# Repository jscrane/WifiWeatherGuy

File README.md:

View this project on [CADLAB.io](https://cadlab.io/project/1280). 

# WiFiWeatherGuy
WeatherGuy for ESP8266.

## Hardware
- Wemos D1 Mini
- ILI9163-based TFT display, see [here](http://henrysbench.capnfatz.com/henrys-bench/arduino-displays/arduino-1-44-in-spi-tft-display-tutorial/)

## Software
- Arduino 1.8.9
- [TFT_eSPI library](https://github.com/Bodmer/TFT_eSPI) 2.5.43
- [ESP8266 for Arduino](https://github.com/esp8266/Arduino.git) 3.1.2
- [Arduino ESP8266 filesystem uploader](https://github.com/esp8266/arduino-esp8266fs-plugin)
- [ArduinoJson](http://arduinojson.org/) 7.2.0
- [Timezone](https://github.com/JChristensen/Timezone) 1.2.4
- [Time](https://github.com/PaulStoffregen/Time) 1.6
- [SimpleTimer](https://github.com/schinken/SimpleTimer)

## Installation
- Get an API key for your Provider (required for OpenWeatherMap, not for Open Meteo)
- Edit data/config.json with your preferences
- Configure your display in TFT_eSPI/User_Setup.h (if using the Arduino IDE), otherwise edit Makefile
- Configure your timezone in zone.h
- Upload the filesystem (Tools > ESP8266 Sketch Data Upload)
- Upload the sketch

## Note
The weather icons must be 24-bit bitmaps; convert from GIF as follows:

    % convert foo.gif -type truecolor foo.bmp 

The [Airycon](https://github.com/HaroleDev/Airycons) icons used by the Open Meteo provider were
converted using the GIMP, exporting the PNG files as 24-bit BMPs.

## Providers

### Open Weather Map
A previously supported provider was [OpenWeatherMap](https://openweathermap.org).

However as-of 2024-11-04 its version 2.5 API is deprecated in favour of version 3.0 which
requires registration of a credit card.

Limitations of this API are:
- astronomy: moon age, phase
- forecasts: forecasts in the free API are every 3 hours and you get 40 of
them, which is too big to parse on an ESP8266
- the credit-card thing

Its code remains for reference, for now.

### Open Meteo
The latest provider is [Open-Meteo](https://open-meteo.com/en/docs).

Limitations of this API are:
- astronomy: moon age, phase
- no forecast humidity

### Meterologisk
If bad things happen to Open Meteo, the next provider is
[Meterologisk](https://github.com/jscrane/WifiWeatherGuy/issues/27).

## Credits
- Javascript [transparency](https://github.com/leonidas/transparency)
- WMO [icons](https://weather-sense.leftium.com/wmo-codes)

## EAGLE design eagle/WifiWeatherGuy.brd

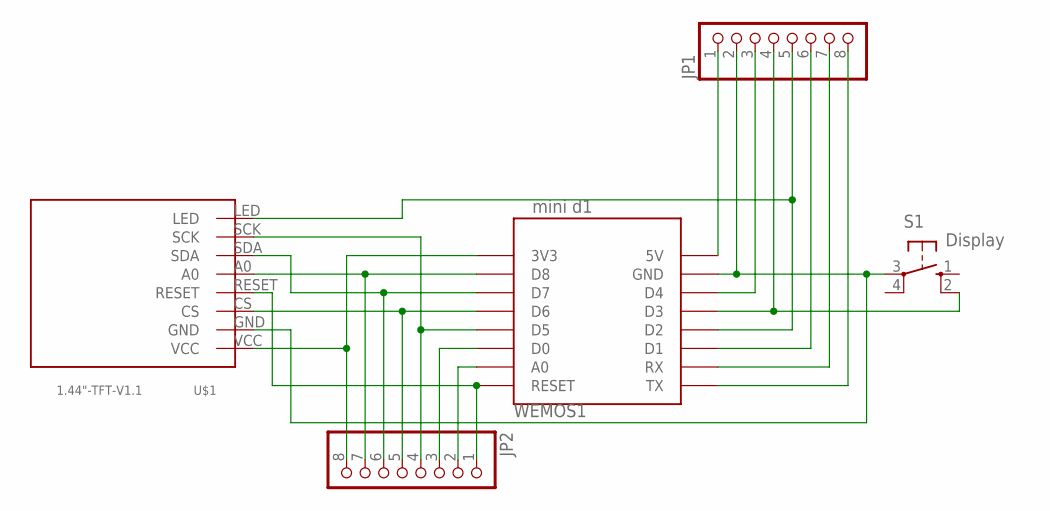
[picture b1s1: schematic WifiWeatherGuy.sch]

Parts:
JP1, JP2: PINHD-1X8; 1X08
S1: Display; B3F-10XX
U$1: 1.44"-TFT-V1.1; 1.44-TFT-V1.1
WEMOS1: mini d1; WEMOS-D1-MINI

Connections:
unnamed: JP2.8, U$1.VCC, WEMOS1.3V3
unnamed: JP2.5, U$1.CS, WEMOS1.D6
unnamed: JP2.7, U$1.A0, WEMOS1.D8
unnamed: JP2.6, U$1.SDA, WEMOS1.D7
unnamed: JP2.4, U$1.SCK, WEMOS1.D5
unnamed: JP1.5, U$1.LED, WEMOS1.D2
unnamed: JP2.3, WEMOS1.D0
unnamed: JP2.1, U$1.RESET, WEMOS1.RESET
unnamed: JP1.4, S1.2 (S1), WEMOS1.D3
unnamed: JP1.1, WEMOS1.5V
unnamed: JP1.3, WEMOS1.D4
unnamed: JP1.6, WEMOS1.D1
unnamed: JP1.7, WEMOS1.RX
unnamed: JP1.8, WEMOS1.TX
unnamed: JP2.2, WEMOS1.A0
unnamed: JP1.2, S1.3, U$1.GND, WEMOS1.GND

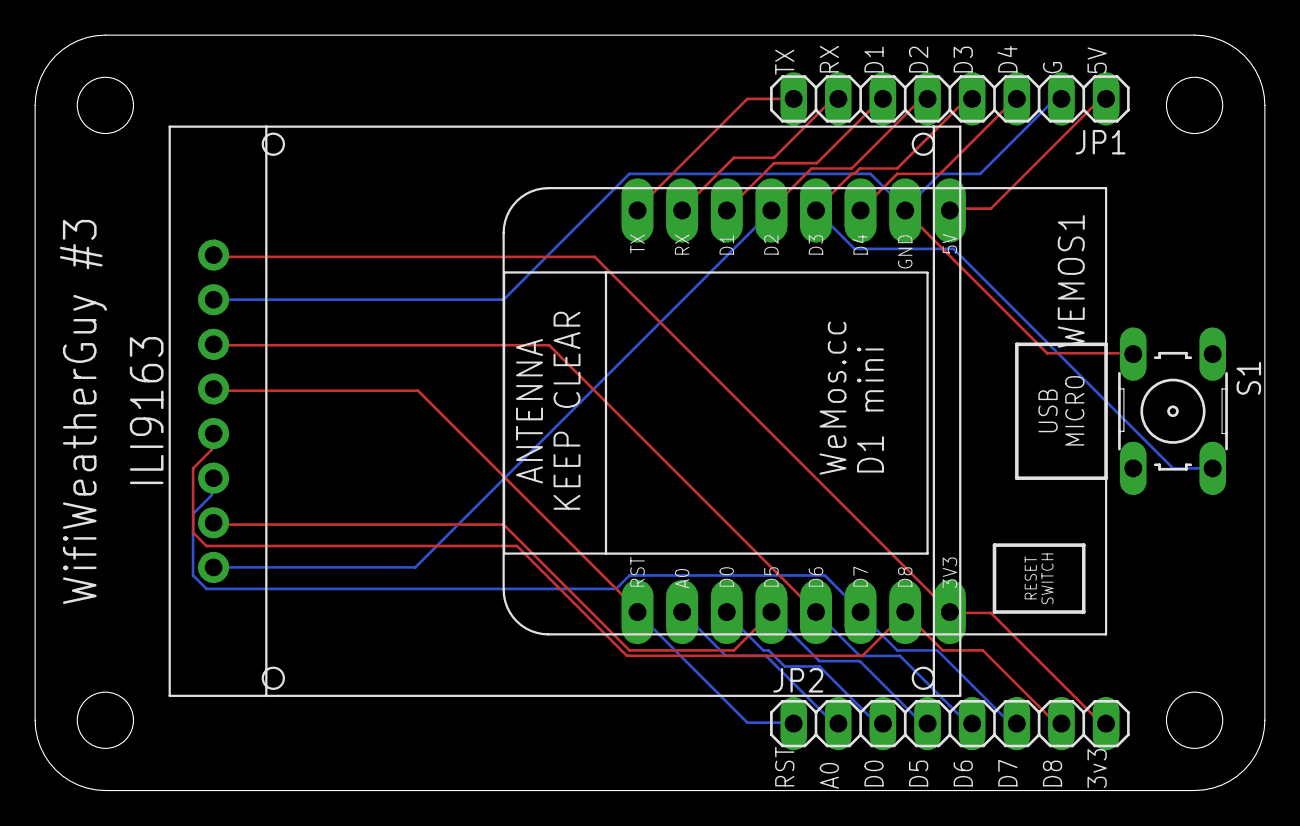
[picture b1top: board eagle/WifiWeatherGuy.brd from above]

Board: 2 copper layers, 70.0 x 43.0 mm, 6 parts (0 on the bottom side), 16 nets.

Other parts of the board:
U$2: DP7043_V1

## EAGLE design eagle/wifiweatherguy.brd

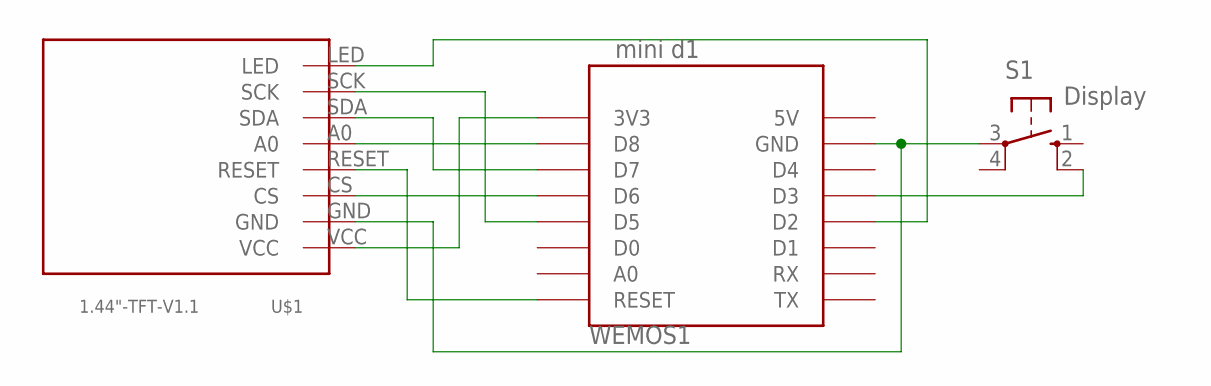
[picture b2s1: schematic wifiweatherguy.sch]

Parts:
S1: Display; B3F-10XX
U$1: 1.44"-TFT-V1.1; 1.44-TFT-V1.1
WEMOS1: mini d1; WEMOS-D1-MINI

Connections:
unnamed: U$1.VCC, WEMOS1.3V3
unnamed: U$1.CS, WEMOS1.D6
unnamed: U$1.A0, WEMOS1.D8
unnamed: U$1.SDA, WEMOS1.D7
unnamed: U$1.SCK, WEMOS1.D5
unnamed: U$1.LED, WEMOS1.D2
unnamed: S1.3, U$1.GND, WEMOS1.GND
unnamed: U$1.RESET, WEMOS1.RESET
unnamed: S1.2 (S1), WEMOS1.D3

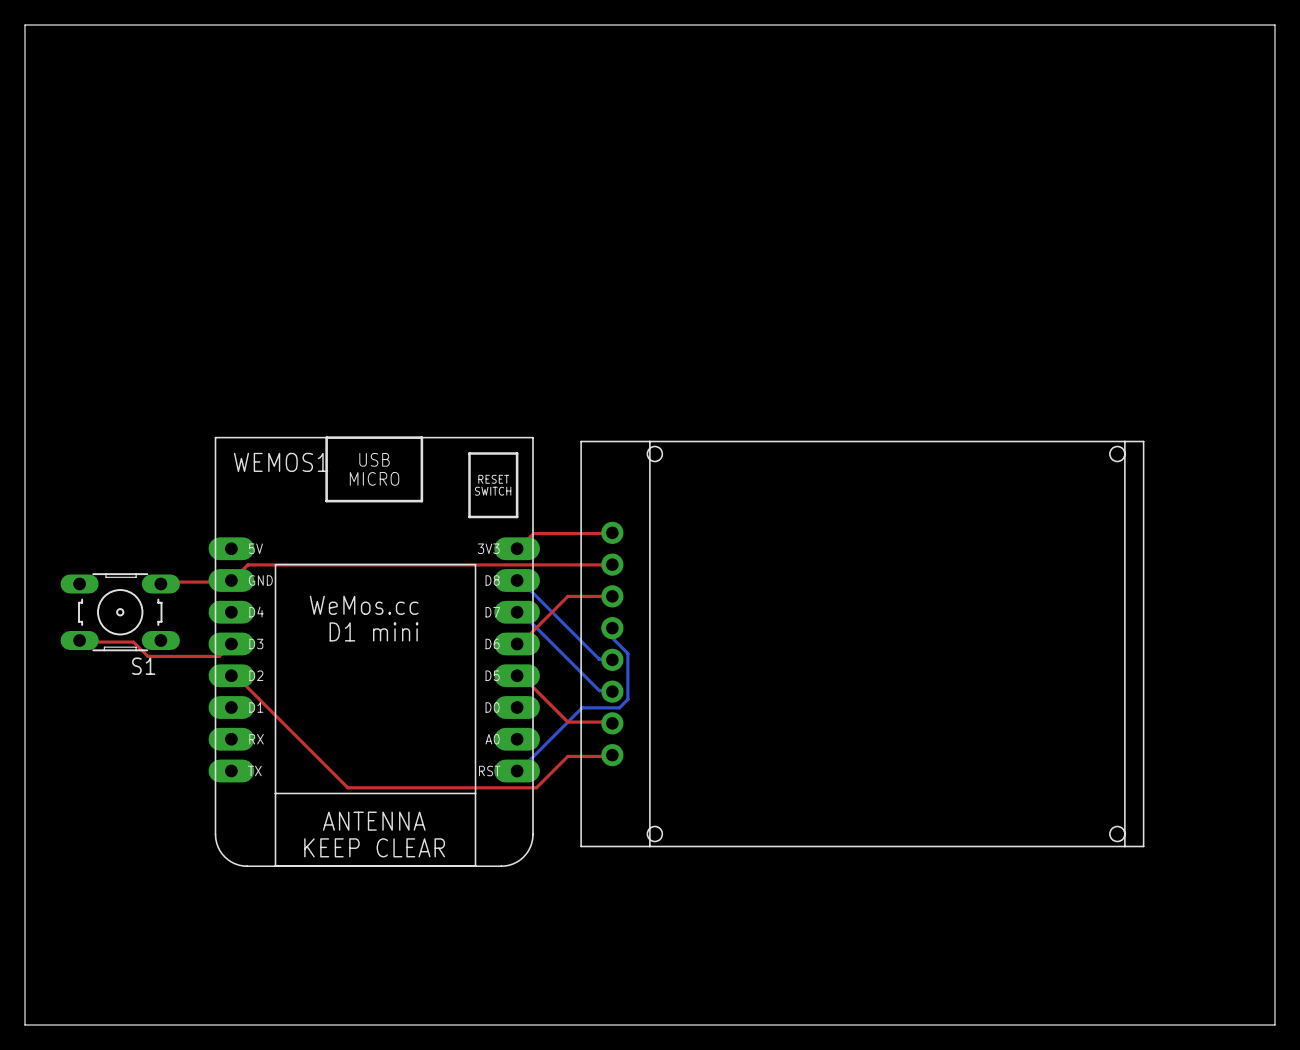
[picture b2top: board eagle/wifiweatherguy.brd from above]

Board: 2 copper layers, 100.0 x 80.0 mm, 3 parts (0 on the bottom side), 9 nets.

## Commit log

2017-08-29 initial
2017-08-29 add todo
2017-08-29 turn off display after 30s
2017-08-30 config
2017-08-30 OTA + mDNS
2017-08-31 add schematic
2017-08-31 eagle
2017-09-05 tiny fixes
2017-10-10 update layout
2017-10-10 add moon-age icons
2017-10-10 renaming
2017-10-10 restore
2017-10-10 test
2017-10-10 24-bit icons
2017-10-10 add astronomy screen
2017-10-10 bugifx
2017-10-10 switch time
2017-10-11 bugfix
2017-10-11 forecast screens
2017-10-11 separate intervals for fetching conditions and forecasts
2017-10-11 change screen order
2017-10-12 refactoring
2017-10-16 Configuration
2017-10-16 hostname and mDNS
2017-10-17 initial config webserver
2017-10-17 Revert "foo"
    This reverts commit fdb8c502c89abde9c2a589aa2e289df4e479be5d.
2017-10-17 Revert "initial config webserver"
    This reverts commit efaf6ef058dbe314636bdc0de18a4fd0c97a1003.
2017-10-17 webserver
2017-10-18 config as json
2017-10-18 viewing config
2017-10-19 form
2017-10-19 updating config via webpage
2017-10-19 refactor
2017-10-19 checkbox
2017-10-20 cleanup
2017-11-01 set WiFi hostname correctly
2017-11-02 debug
2017-11-02 replace ArduinoOTA with HTTPUpdateServer
2017-11-03 add upgrade button
2017-11-06 reset to current conditions on fade out
2017-11-08 setup AP for initial config
2017-11-08 rotation
2017-11-08 cleanup AP code
2017-11-19 reboot after update config
2018-01-06 display astronomy after current conditions
2018-01-06 enable serial debugging if button pressed at startup
2018-01-06 break out gerbers
2018-01-08 v2 gerbers
2018-01-12 PROGMEM string constants; don't update display unless epoch changes; WifiClient memory leak fix
2018-01-12 put more strings in flash
2018-01-12 more flash strings
2018-01-14 more defaults for missing fields; timeout on http fetch
2018-01-15 more heap debugging; add config defaults
2018-01-16 bugfixes and improvements
2018-01-17 age of moon in [0, 30)
2018-02-20 Delete TODO.md
    use "issues" instead
2018-02-20 always enable mdns
2018-02-25 strlcpy; adaptive buffer size
2018-02-27 defensive
2018-02-27 buffer size
2018-02-27 don't use String
2018-03-02 auto wificlient; snooze delay
2018-03-03 configure retry_interval
2018-03-06 attachInterrupt
2018-03-09 PWM is 0..1023
2018-03-11 TFT display info.
2018-03-11 pinout
2018-03-12 tabs
2018-03-12 add HAVE_PWM
2018-03-12 gitignore
2018-03-13 minor changes
2018-03-13 add dimmable flag
2018-03-17 switch to TFT_eSPI
2018-03-17 add missing moon bmp
2018-03-17 clear screen on start
2018-03-21 tiny bugfix
2018-05-29 tiny update
2018-05-29 tiny change
2018-06-07 autoreconnect
2018-06-07 variable
2018-06-08 formatting
2018-06-08 nighttime icons
2018-08-17 TFT_eSPI instructions
2018-09-07 cleanups
2018-09-07 add wemos pin headers
2018-09-07 Backlink to CADLAB.io has been added.
2018-09-07 update to v3
2018-09-08 v3 gerbers
2018-09-08 add statistics screen
2018-09-10 fix #11
2018-10-14 more constants
2018-10-15 move high-level display functions into display.cpp
2018-10-23 fix #13
2018-10-24 optionally use nearest weather station
2018-10-26 remove magic numbers
2018-10-30 temp must be greater than chill
2018-11-16 fix #14 captive portal
2018-11-17 add charset
2018-11-17 send 200 before restarting
2018-12-18 add Makefile flags
2019-01-13 add help
2019-01-13 info icon
2019-02-01 update deps
2019-03-08 break out wunderground
2019-03-08 add scaffolding for Open Weather Map
2019-03-10 add openweathermap support
2019-03-10 nearest
2019-03-10 owm bugfixes
2019-03-11 wind direction
2019-03-11 openweathermap forecasts
2019-03-11 openweathermap disadvantages
2019-03-17 description must fit on screen
2019-03-17 add providers
2019-04-13 fix #17
2019-04-13 fix #18
2019-04-13 store strings in flash
2019-05-08 display day
2019-05-12 update dependency
2019-05-31 updates for new uC-makefile
2019-06-01 fix #21
2019-06-06 annotation
2019-06-08 update ArduinoJson to v6.x; improve debugging
2019-06-14 boot animation
2019-06-15 add timers and startors; remove retry interval
2019-11-09 library deps update
2019-12-10 add default provider if undefined for arduino ide compatibility
2019-12-13 more arduino compat
2019-12-18 adding timezone support
2019-12-18 missing file
2019-12-19 restructure loop() using timers
2019-12-19 fix #22
2020-05-15 replace Stator with Switch
2020-05-17 fix captive portal
2020-05-20 nearest is default
2020-05-25 fix #23
2020-07-08 support alternative display
2020-07-08 support different font sizes
2020-08-03 update core dependency
2020-09-23 fix #24
2021-02-19 support esp8bit
2021-02-26 use nice font with larger screen
2021-05-17 platform + library updates
2021-09-25 add PREBUILD
2023-01-22 bugfix for non-dimmable display
2024-11-09 refactor + openmeteo client
2024-11-09 flash strings
2024-11-09 ArduinoJson v7
2024-11-09 remove debugging
2024-11-09 remove cruft
2024-11-09 make icon size configurable from Makefile
2024-11-09 update daytime icons
2024-11-09 add nighttime icons
2024-11-09 retire wunderground provider
2024-11-09 small bugfixes
2024-11-10 geocoding api
2024-11-10 openmeteo responses are in local time already
2024-11-10 remove summer/winter config for openmeteo
2024-11-10 bugfixes
2024-11-10 26 open meteo provider (#28)
    - Open Meteo client
    - Remove Wunderground client
    - New icons from Airycons
    - ArduinoJson v7
2024-11-10 refactor JsonClient
2024-11-11 more fun with lambdas

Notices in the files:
eagle/WifiWeatherGuy.brd:
(c) 2018 Steve
